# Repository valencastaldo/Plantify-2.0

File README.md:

# Plantify

## Maceta Inteligente — Monitor Ambiental de Salud

**Hunter Electronics · 2026**

---

## ¿Qué es Plantify?

Plantify es un dispositivo de **monitoreo ambiental preventivo** integrado en una maceta inteligente, desarrollado sobre la plataforma **ESP32**. El sistema monitorea de forma continua las condiciones del ambiente interior donde vive el usuario, utilizando sensores ambientales para detectar situaciones que pueden afectar el confort y el bienestar.

La planta no es el producto final, sino el elemento físico que integra el sistema dentro del hogar. Mientras contribuye al ambiente mediante su proceso natural de intercambio gaseoso, el **ESP32** procesa los datos obtenidos por los sensores y genera alertas mediante un **semáforo LED RGB, una pantalla OLED, un buzzer y notificaciones push a través de la aplicación Blynk**.

El sistema busca facilitar la identificación de condiciones ambientales desfavorables y permitir que el usuario pueda tomar medidas preventivas, como ventilar el ambiente o corregir condiciones de humedad y temperatura.

> **"Tu planta cuida tu salud"**

---

## 🏥 Relación con la salud

La calidad del ambiente interior puede influir en el confort, el descanso y el bienestar de las personas. Factores como la **temperatura, la humedad y la calidad del aire** deben mantenerse dentro de niveles adecuados para evitar condiciones ambientales desfavorables.

Plantify utiliza el **BME680**, un sensor ambiental integrado capaz de medir **temperatura, humedad relativa, presión atmosférica y resistencia del gas**, permitiendo obtener información relacionada con la calidad del aire. Además, incorpora un **LDR** para medir la iluminación ambiental y un sensor de humedad del suelo para controlar las condiciones del sustrato de la planta.

| Sensor              | Variable                   | Rango/condición objetivo                 | Efecto o acción preventiva                                                          |
| ------------------- | -------------------------- | ---------------------------------------- | ----------------------------------------------------------------------------------- |
| **BME680**          | Temperatura                | 18 – 26 °C                               | Detectar condiciones térmicas desfavorables                                         |
| **BME680**          | Humedad relativa           | 40 – 60 %                                | Reducir condiciones que favorezcan sequedad, condensación o proliferación de hongos |
| **BME680**          | Calidad del aire (VOC/gas) | Según medición y línea base del ambiente | Detectar cambios en la calidad del aire y recomendar ventilación                    |
| **BME680**          | Presión atmosférica        | Monitoreo continuo                       | Registrar cambios en las condiciones ambientales                                    |
| **LDR**             | Luz ambiental              | Nivel adecuado durante el día            | Controlar las condiciones de iluminación de la planta                               |
| **Sensor de suelo** | Humedad del sustrato       | 40 – 60 %                                | Evitar falta o exceso de agua en la planta                                          |

> **Nota:** El BME680 no mide directamente CO₂ en ppm. Su medición de gases se utiliza para estimar cambios en la calidad del aire mediante VOC y resistencia del gas. Por este motivo, Plantify no debe presentar la lectura del BME680 como una medición directa de CO₂.

---

## ⚙️ Funcionamiento del sistema

El funcionamiento general de Plantify se basa en la siguiente secuencia:

1. Los sensores recopilan información del ambiente y del sustrato.
2. El **ESP32** recibe y procesa los datos.
3. El sistema compara las mediciones con los valores de referencia establecidos.
4. El **LED RGB** indica visualmente el estado ambiental.
5. La **pantalla OLED** muestra los valores medidos.
6. El **buzzer** genera una alerta cuando se detecta una condición desfavorable.
7. La aplicación **Blynk** permite visualizar los datos y recibir notificaciones.
8. El sensor de humedad del suelo permite controlar el estado de la planta y determinar cuándo necesita riego.

---

## 🔧 Componentes principales

* **ESP32 DevKitC**
* **BME680**
* **LDR**
* **Sensor de humedad del suelo**
* **Pantalla OLED**
* **LED RGB**
* **Buzzer**
* **Bomba de agua**
* **Módulo relé**
* **Maceta y planta**
* Fuente de alimentación

---

## 📱 Aplicación Blynk

Plantify utiliza **Blynk** como interfaz de monitoreo remoto. Desde la aplicación, el usuario puede consultar los valores registrados por el sistema y recibir notificaciones cuando se detecten condiciones ambientales que requieran atención.

Entre los datos que pueden visualizarse se encuentran:

* Temperatura.
* Humedad relativa.
* Calidad relativa del aire mediante VOC/gas.
* Presión atmosférica.
* Nivel de iluminación.
* Humedad del suelo.
* Estado general del ambiente.

---

## 🌱 Objetivo

El objetivo principal de Plantify es desarrollar una solución tecnológica capaz de **monitorear las condiciones ambientales de un espacio interior y proporcionar información preventiva al usuario**, integrando electrónica, programación, sensores IoT y una interfaz móvil en un único dispositivo.

---

## 👥 Integrantes

**Jeronimo Capozzolo**
**Valentino Castaldo**
**Joaquin Bargach**
**Dylan Dragneff**

**7°6° · 2026**

**Hunter Electronics**

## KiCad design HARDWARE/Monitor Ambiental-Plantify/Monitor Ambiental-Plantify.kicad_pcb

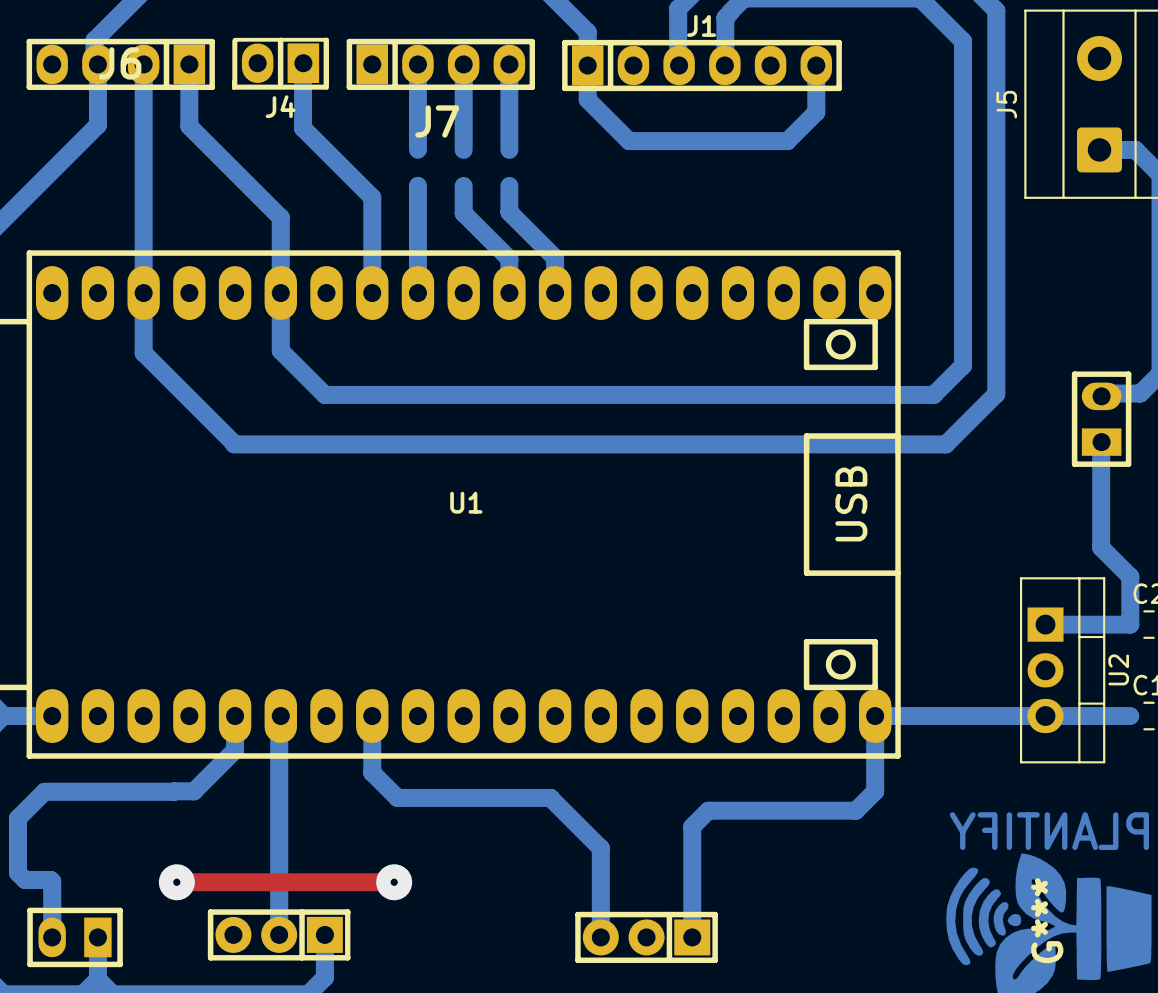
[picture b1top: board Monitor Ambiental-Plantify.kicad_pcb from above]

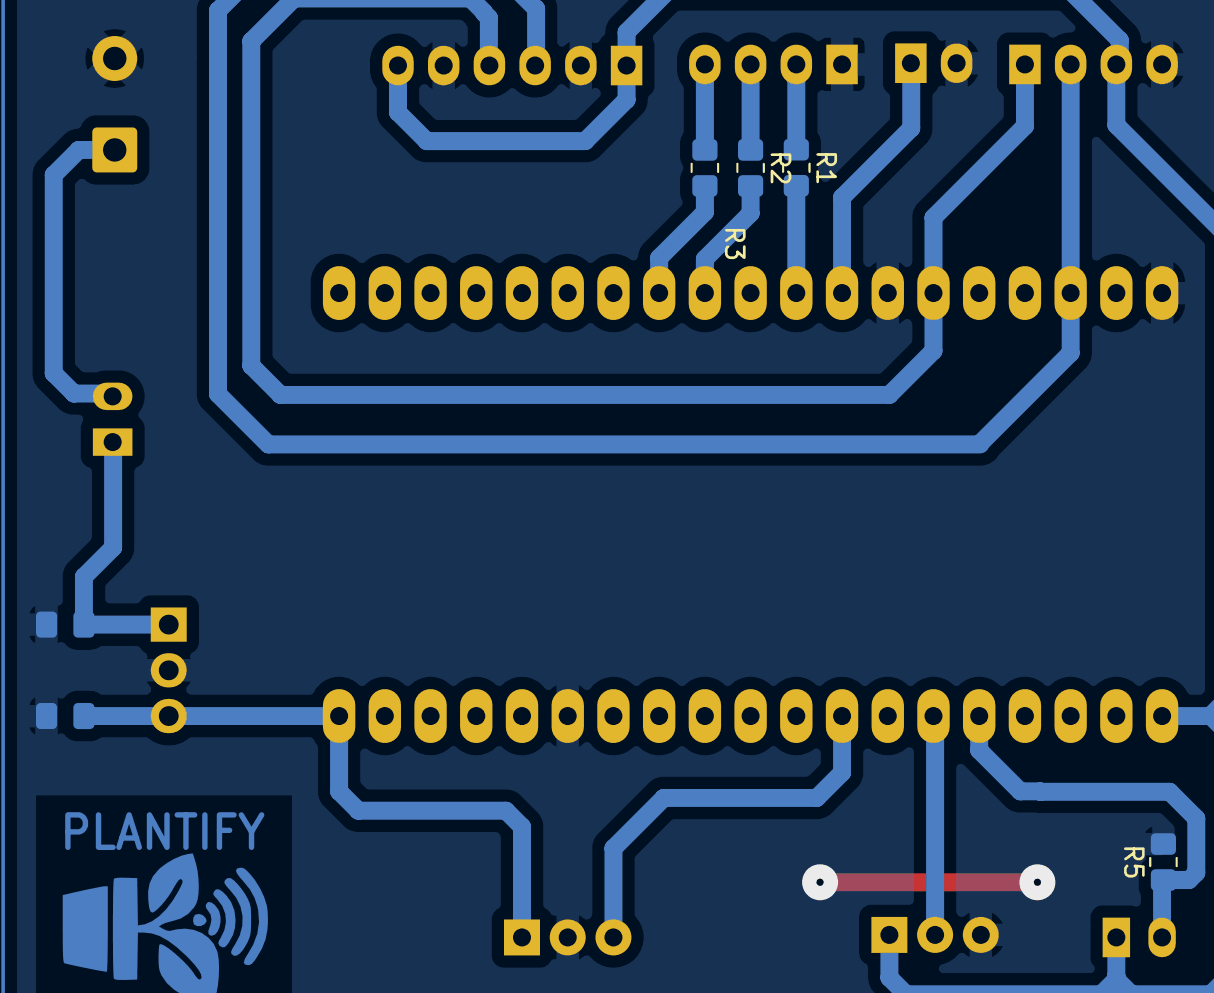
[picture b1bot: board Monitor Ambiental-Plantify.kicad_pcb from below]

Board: 2 copper layers, 17 parts (4 on the bottom side), 17 nets.

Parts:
C1, C2: C; C_0805_2012Metric_Pad1.18x1.45mm_HandSolder
J1: Conn_01x06_Pin; pin_strip_6
J3, J8: Conn_01x03_Pin; Pin_Strip_3
J4: Conn_01x02_Pin; Pin_Header_2
J5: Screw_Terminal_01x02; TerminalBlock_MetzConnect_Type101_RT01602HBWC_1x02_P5.08mm_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
J6, J7: Conn_01x04_Pin; pin_strip_4
R1, R2, R3, R5: R; R_0805_2012Metric_Pad1.20x1.40mm_HandSolder
R4: R_Photo; Pin_strip_2
SW1: SW_SPDT; Jumper
U1: ESP32_DEVKITC
U2: LM7805_TO220; TO-220-3_Vertical

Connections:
+3.3V: J1.1, J1.6, J3.1, J6.3, R4.1, U1.1 (3V3)
+5V: C1.1, J8.1, U1.19 (5V), U2.3 (VO)
B: R3.2, U1.27 (IO16)
G: R2.2, U1.28 (IO17)
GND: C1.2, C2.2, J1.2, J1.5, J3.3, J4.2, J5.2, J6.4, J7.1, J8.2, R5.2, U1.14 (GND), U1.32 (GND), U1.38 (GND), U2.2 (GND)
LDR: R4.2, R5.1, U1.5 (IO34)
unnamed: J7.2, R1.1
unnamed: J7.3, R2.1
unnamed: J7.4, R3.1
R: R1.2, U1.30 (IO18)
SCL: J1.3, J6.2, U1.36 (IO22)
SDA: J1.4, J6.1, U1.33 (IO21)
VCC: C2.1, SW1.1 (A), U2.1 (VI)
VIN: J5.1, SW1.2 (B)
buzzer+: J4.1, U1.31 (IO19)
relay: J8.3, U1.8 (IO33)
suelo: J3.2, U1.6 (IO35)
